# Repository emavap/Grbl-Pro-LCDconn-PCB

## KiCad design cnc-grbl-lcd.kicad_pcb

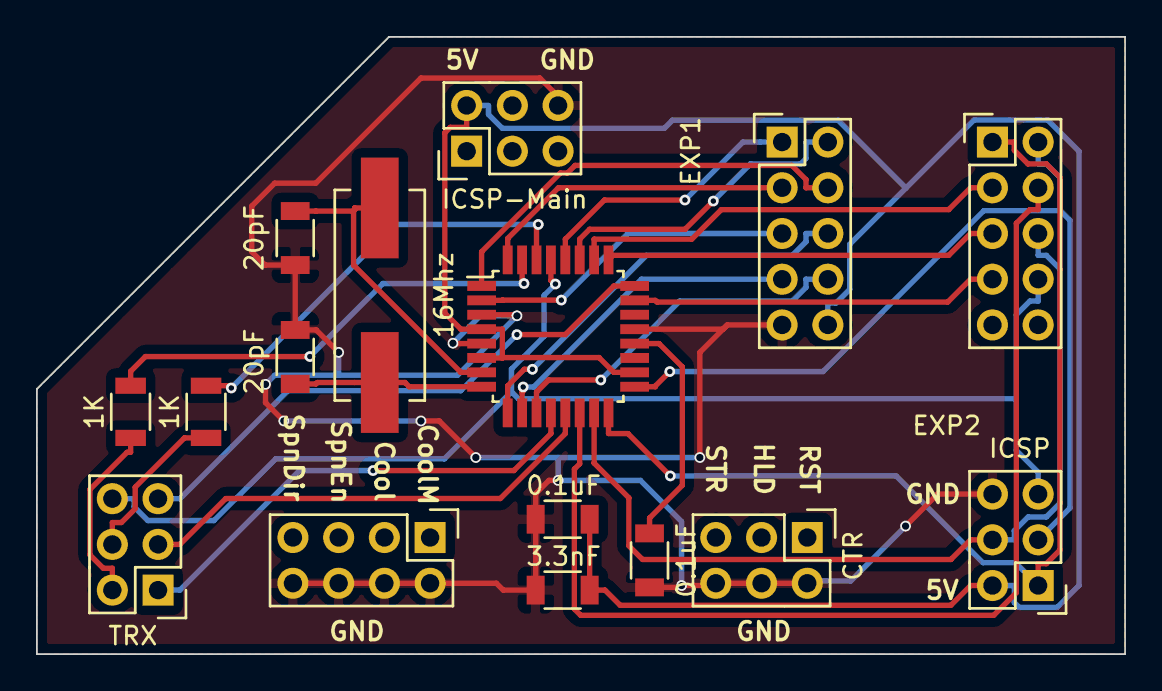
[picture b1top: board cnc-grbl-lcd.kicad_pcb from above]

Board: 2 copper layers, 60.5 x 34.3 mm, 16 parts (0 on the bottom side), 28 nets.

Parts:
C1, C2: 0.1uF; C_1206
C3: 3.3nF; C_1206
C7, C8: 20pF; C_1206
IC1: ATMEGA328P-A; TQFP-32_7x7mm_Pitch0.8mm
P1: ICSP-Main; Pin_Header_Straight_2x03
P2: ICSP; Pin_Header_Straight_2x03
P3: EXP1; Pin_Header_Straight_2x05
P4: EXP2; Pin_Header_Straight_2x05
P11: CTR; Pin_Header_Straight_2x03
P12: CON; Pin_Header_Straight_2x04
P13: TRX; Pin_Header_Straight_2x03
R3, R4: 1K; R_1206
Y1: 16Mhz; Crystal_HC49-SD_SMD

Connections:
+5V: C1.2, C3.1, IC1.4, IC1.6, IC1.18, P1.2, P2.2, P3.10
BTN_EN1: IC1.25, P4.5
BTN_EN2: IC1.26, P4.3
BTN_enc: IC1.27, P3.2
Beeper: IC1.28, P3.1
GND: C1.1, C2.2, C3.2, C7.2, C8.2, IC1.3, IC1.5, IC1.21, P1.6, P2.6, P3.9, P11.2, P11.4, P11.6, P12.2, P12.4, P12.6, P12.8
LCD4: IC1.2, P3.5
LCD5: IC1.9, P3.6
LCD6: IC1.10, P3.7
LCD7: IC1.11, P3.8
LCDE: IC1.32, P3.3
LCDRS: IC1.1, P3.4
MISO: IC1.16, P2.1, P4.1
MOSI: IC1.15, P2.4, P4.6
unnamed: C2.1, IC1.20
unnamed: C7.1, IC1.7, Y1.2
unnamed: C8.1, IC1.8, Y1.1
unnamed: IC1.30, R3.1
unnamed: IC1.31, R4.1
RX: IC1.13, P13.3
RX_FTDI: P13.4, R3.2
SCK: IC1.17, P2.3, P4.2
SD_CSEL: IC1.14, P4.4
SD_DET: IC1.23, P4.7
TX: IC1.12, P13.1
TX_FTDI: P13.2, R4.2
reset: IC1.24, P13.5
reset-ftdi: IC1.29, P2.5, P4.8, P13.6

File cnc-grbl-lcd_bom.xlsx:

Id | Designator | Package | Quantity | Designation | Supplier and ref
1 | C1,C2 | C_1206 | 2 | 0.1uF | Ceramic Capacitor 0.1uF 1206
2 | C3 | C_1206 | 1 | 3.3nF | Ceramic Capacitor 3.3nF 1206
3 | C7,C8 | C_1206 | 2 | 20pF | Ceramic Capacitor 20pF 1206
4 | IC1 | TQFP-32_7x7mm_Pitch0.8mm | 1 | ATMEGA328P-AU | http://be.farnell.com/atmel/atmega328p-au/mcu-8bit-atmega-20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
5 | P1 | Pin_Header_Straight_2x03 | 1 | ICSP-Main | https://www.aliexpress.com/item/Free-Shipping-50-Pieces-lot-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 | Only to understand I cannot find the component on farnell
6 | R3,R4 | R_1206 | 2 | 1K | Resistor 1k 1206
7 | P11 | Pin_Header_Straight_2x03 | 1 | CTR | https://www.aliexpress.com/item/Free-Shipping-50-Pieces-lot-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 | Only to understand I cannot find the component on farnell
8 | Y1 | Crystal_HC49-SD_SMD | 1 | 16Mhz | http://be.farnell.com/webapp/wcs/stores/servlet/ProductDispl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
9 | P12 | Pin_Header_Straight_2x04 | 1 | CON | http://www.ebay.com/itm/20pcs-2-54mm-2x4-8pin-11mm-Long-Legs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 | Only to understand I cannot find the component on farnell
10 | P13 | Pin_Header_Straight_2x03 | 1 | TRX | http://be.farnell.com/harwin/m20-9980346/connector-header-th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
11 | P2 | Pin_Header_Straight_2x03 | 1 | ICSP | http://be.farnell.com/harwin/m20-9980346/connector-header-th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
12 | P3 | Pin_Header_Straight_2x05 | 1 | EXP1 | http://be.farnell.com/webapp/wcs/stores/servlet/ProductDispl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
13 | P4 | Pin_Header_Straight_2x05 | 1 | EXP2 | http://be.farnell.com/webapp/wcs/stores/servlet/ProductDispl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

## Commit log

2017-12-17 PCB tested and working
